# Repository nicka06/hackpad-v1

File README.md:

NICK'S HACK PAD

Nick's Hack pad is a 5 key macropad allowing individuals to utilize 8 keys (or macros) while only using one hand. 

Features:

Beautifully designed case (although it may look like an item that americans are known for)

Incredible design (with 4 keys for the four fingers and one for your thumb)

Easy to change firmware with just a few clicks to change what the hackpad does. 

CAD Model:

Everything fits together using 6 M3 Bolts . All of which go on the outside of the case. 

The Cad model has two parts. The base which is where the pcb sits and the top which snaps on to make it a cleaner look. 

PCB Schematic

Made in Keycad

PCB
Here's my PCB! It was made in KiCad. 

BOM:
Here should be everything you need to make this hackpad

5x Cherry MX Switches

5x DSA Keycaps

6X M3x12mm SHCS Bolts

1x Case (2 printed parts)

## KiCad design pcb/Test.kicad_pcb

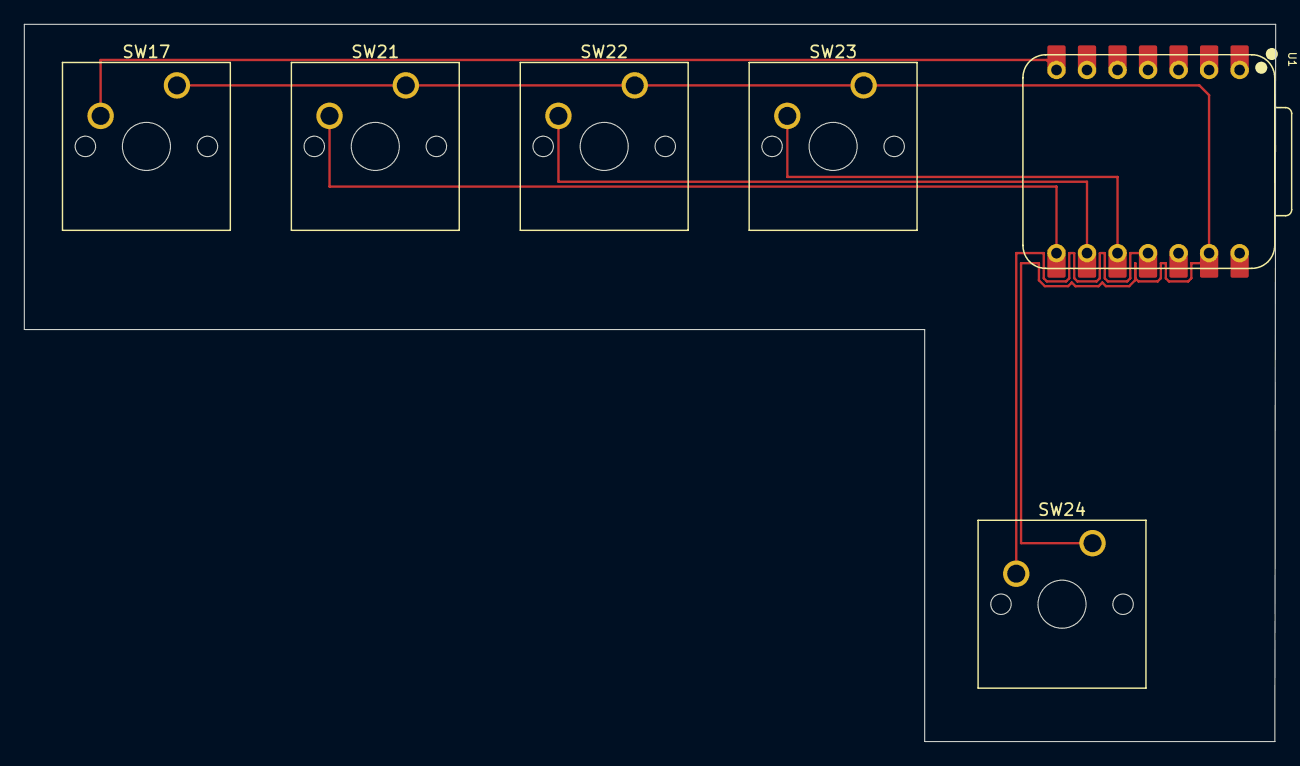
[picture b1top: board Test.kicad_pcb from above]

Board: 2 copper layers, 104.1 x 59.7 mm, 6 parts (0 on the bottom side), 6 nets.

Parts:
SW17, SW21, SW22, SW23, SW24: SW_Push; SW_Cherry_MX_1.00u_PCB
U1: XIAO-RP2040-DIP

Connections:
GND: SW17.1, SW21.1, SW22.1, SW23.1, SW24.1, U1.13 (GND)
unnamed: SW17.2, U1.7 (GPIO0/TX)
unnamed: SW21.2, U1.8 (GPIO1/RX)
unnamed: SW22.2, U1.9 (GPIO2/SCK)
unnamed: SW24.2, U1.11 (GPIO3/MOSI)
unnamed: SW23.2, U1.10 (GPIO4/MISO)

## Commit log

2025-06-30 Finished v1 of hackpad
2025-06-30 Fix .gitignore and remove ignored files from tracking
2025-06-30 Remove embedded git repo from hackpad-v1
2025-06-30 moved readme
2025-06-30 updated :
2025-06-30 Remove .DS_Store files from repository
2025-06-30 added basic firmware
2025-07-01 updated to have new readme as well as restructured files
2025-07-01 testing readme
